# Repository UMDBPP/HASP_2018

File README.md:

# HASP_2018
2018 HASP payload with microphones and a dropped module.

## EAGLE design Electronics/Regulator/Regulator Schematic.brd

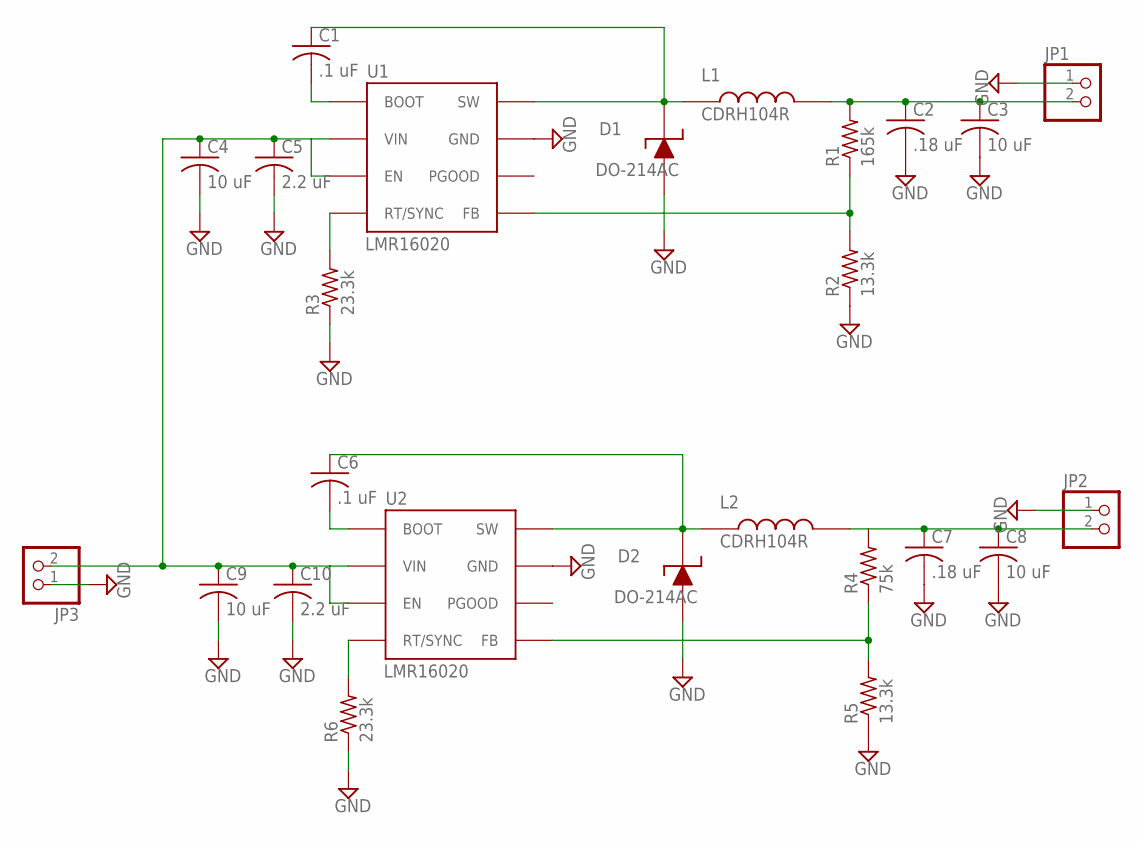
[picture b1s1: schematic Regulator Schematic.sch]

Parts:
C1, C6: .1 uF; C0603
C2, C7: .18 uF; C0603
C3, C8: 10 uF; C0603
C4, C9: 10 uF; C1210
C5, C10: 2.2 uF; C1210
D1, D2: DO-214AC
JP1, JP2, JP3: PINHD-1X2; 1X02
L1, L2: CDRH104R
R1: 165k; R0603
R2, R5: 13.3k; R0603
R3, R6: 23.3k; R0603
R4: 75k; R0603
U1, U2: LMR16020; SO8

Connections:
GND: C2.2, C3.2, C4.2, C5.2, C7.2, C8.2, C9.2, C10.2, D1.P$1, D2.P$1, JP1.1, JP2.1, JP3.1, R2.1, R3.1, R5.1, R6.1, U1.P$7 (GND), U1.PAD (GND), U2.P$7 (GND), U2.PAD (GND)
IN: C4.1, C5.1, C9.1, C10.1, JP3.2, U1.P$2 (VIN), U1.P$3 (EN), U2.P$2 (VIN), U2.P$3 (EN)
unnamed: R6.2, U2.P$4 (RT/SYNC)
unnamed: R3.2, U1.P$4 (RT/SYNC)
unnamed: C1.2, U1.P$1 (BOOT)
unnamed: C1.1, D1.P$2, L1.P$1, U1.P$8 (SW)
unnamed: R1.1, R2.2, U1.P$5 (FB)
unnamed: C6.2, U2.P$1 (BOOT)
unnamed: C6.1, D2.P$2, L2.P$1, U2.P$8 (SW)
unnamed: R4.1, R5.2, U2.P$5 (FB)
unnamed: C2.1, C3.1, JP1.2, L1.P$2, R1.2
unnamed: C7.1, C8.1, JP2.2, L2.P$2, R4.2

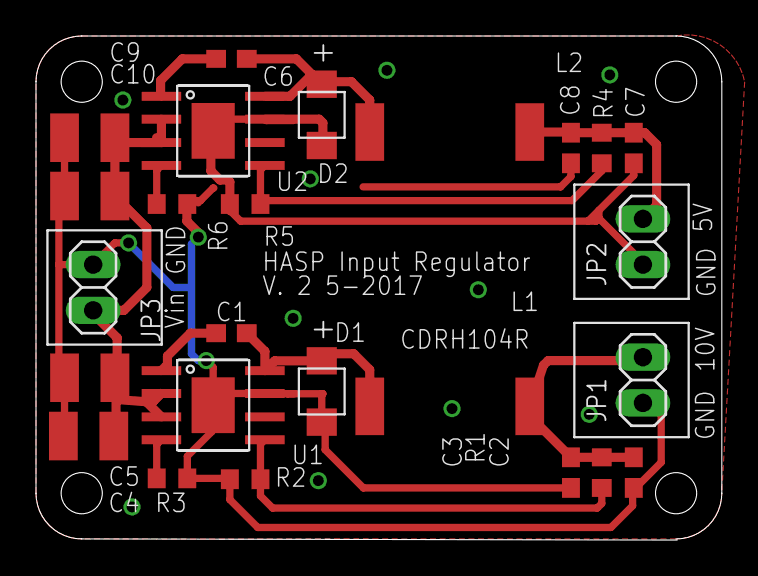
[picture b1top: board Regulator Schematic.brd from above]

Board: 2 copper layers, 38.1 x 28.0 mm, 25 parts (0 on the bottom side), 12 nets.

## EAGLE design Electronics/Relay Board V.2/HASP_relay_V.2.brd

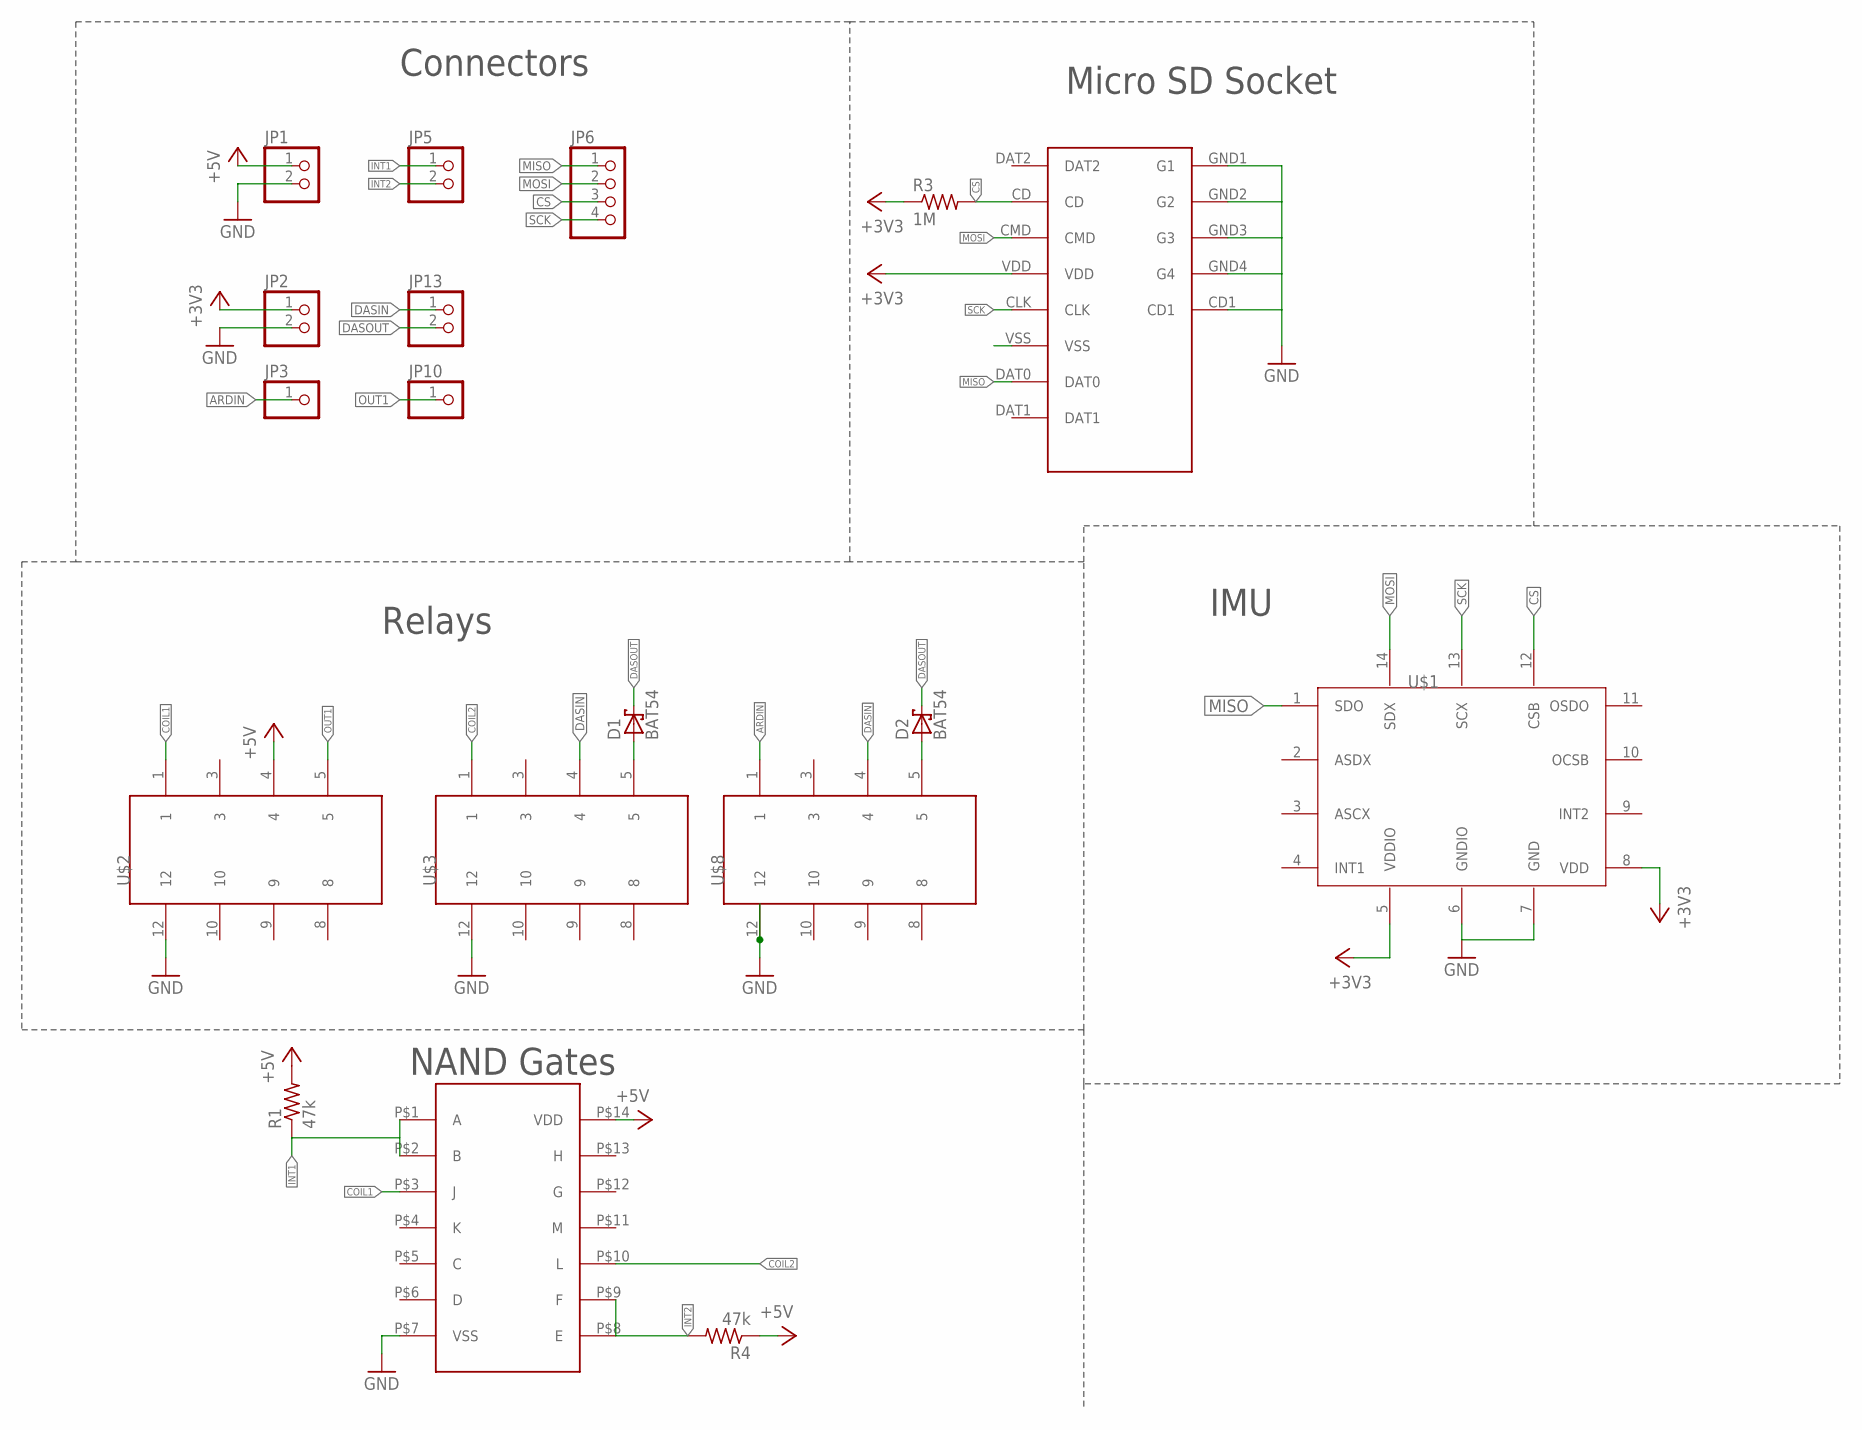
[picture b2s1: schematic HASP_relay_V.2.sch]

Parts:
D1, D2: BAT54; SOT23
JP1, JP2, JP5, JP13: PINHD-1X2; 1X02
JP3, JP10: PINHD-1X1; 1X01
JP6: PINHD-1X4; 1X04
R1, R4: 47k; RESC1608X50N
R3: 1M; R0603
U$1: BMI160; IMU
U$2, U$3, U$8: EC2; EC2-5SNU
U$4: MICRO_SD; MICRO_SD_HINGED
U$5: CD4093BE

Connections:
+3V3: JP2.1, R3.1, U$1.5 (VDDIO), U$1.8 (VDD), U$4.VDD
+5V: JP1.1, R1.2, R4.1, U$2.4, U$5.P$14 (VDD)
ARDIN: JP3.1, U$8.1
COIL1: U$2.1, U$5.P$3 (J)
COIL2: U$3.1, U$5.P$10 (L)
CS: JP6.3, R3.2, U$1.12 (CSB), U$4.CD
DASIN: JP13.1, U$3.4, U$8.4
DASOUT: D1.3 (K), D2.3 (K), JP13.2
GND: JP1.2, JP2.2, U$1.6 (GNDIO), U$1.7 (GND), U$2.12, U$3.12, U$4.CD1, U$4.GND1 (G1), U$4.GND2 (G2), U$4.GND3 (G3), U$4.GND4 (G4), U$5.P$7 (VSS), U$8.12
INT1: JP5.1, U$5.P$1 (A), U$5.P$2 (B)
INT2: JP5.2, R4.2, U$5.P$8 (E), U$5.P$9 (F)
MISO: JP6.1, U$1.1 (SDO), U$4.DAT0
MOSI: JP6.2, U$1.14 (SDX), U$4.CMD
unnamed: D1.1 (A), U$3.5
unnamed: D2.1 (A), U$8.5
OUT1: JP10.1, U$2.5
SCK: JP6.4, U$1.13 (SCX), U$4.CLK

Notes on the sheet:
NAND Gates
Relays
Connectors
IMU
Micro SD Socket

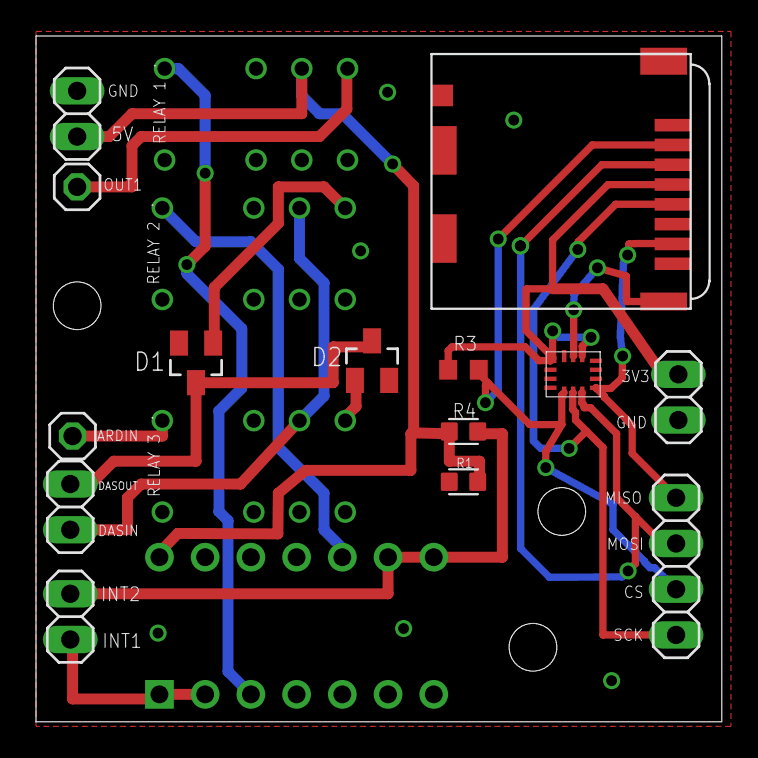
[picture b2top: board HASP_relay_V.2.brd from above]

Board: 2 copper layers, 38.1 x 38.1 mm, 18 parts (0 on the bottom side), 17 nets.

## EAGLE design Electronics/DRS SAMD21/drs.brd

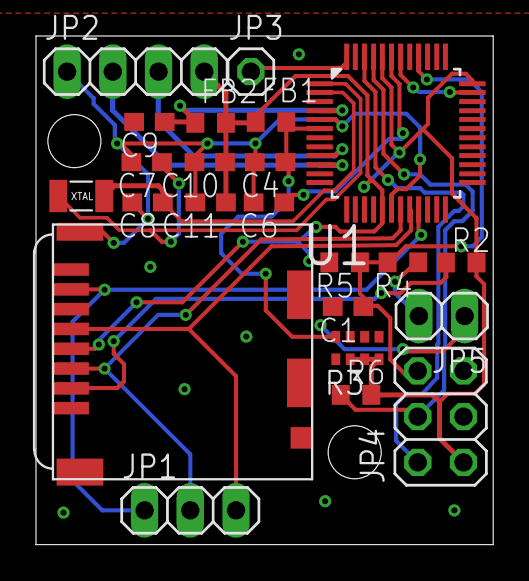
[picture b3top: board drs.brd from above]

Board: 2 copper layers, 25.4 x 28.3 mm, 23 parts (0 on the bottom side), 18 nets.

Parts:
C1, C9: 100nF; C0603
C4: 10uF; C0603
C6: 1uF; C0603
C7, C8, C10, C11: 6.8pF; C0603
FB1, FB2: 0603
JP1: 1X03
JP2: 1X04
JP3: 1X01
JP4: 2X03
JP5: 1X02
R2: 1M; R0603
R3: 100nF; 0603-ARV
R4: 330; R0603
R5, R6: 10k; R0603
U1: ATSAMD21G18; 48-TQFP
U$1: MICRO_SD; MICRO_SD_HINGED
XTAL1: 2-SMD

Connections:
+3V3: C10.1, C11.1, FB1.1, FB2.2, JP2.4, JP4.1, R2.2, R3.2, R3.3, R3.4, R5.2, R6.2, U1.17, U1.36, U1.44, U$1.VDD
AIN1: JP2.3, U1.9
AIN2: JP2.2, U1.10
GND: C1.2, C4.2, C6.2, C7.2, C8.2, C9.2, C10.2, C11.2, JP2.1, JP4.5, JP5.1, R3.1, R3.5, R3.6, R3.7, U1.5, U1.18, U1.35, U1.42, U$1.CD1, U$1.GND1, U$1.GND2, U$1.GND3, U$1.GND4, U$1.VSS
LED: JP3.1, U1.48
MISO: JP1.1, U1.21, U$1.DAT0
MOSI: JP1.2, U1.19, U$1.CMD
unnamed: R2.1, U$1.CD
unnamed: C6.1, U1.43
unnamed: C4.1, FB1.2, R3.8, U1.6
unnamed: JP5.2, R4.1
RESET: C1.1, JP4.6, R4.2, R5.1, U1.40
SCK: JP1.3, U1.20, U$1.CLK
SWDCLK: JP4.4, R6.1, U1.45
SWDIO: JP4.2, U1.46
VREFA: C9.1, FB2.1, U1.4
XIN32: C7.1, U1.1, XTAL1.P2
XOUT32: C8.1, U1.2, XTAL1.P1

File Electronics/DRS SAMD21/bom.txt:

Partlist exported from C:/UMD/BPP/HASP/2018/HASP_2018/Electronics/DRS SAMD21/drs.sch at 7/9/2018 5:26

Qty Value       Device                 Package         Parts            Description                
1               ABS07AIG-32.768KHZ-1-T 2-SMD           XTAL1                                       
1               C-USC0603              C0603           C1               CAPACITOR, American symbol 
2               FERRITE_BEAD-0603      0603            FB1, FB2                                    
1               PINHD-1X1              1X01            JP3              PIN HEADER                 
1               PINHD-1X2              1X02            JP5              PIN HEADER                 
1               PINHD-1X3              1X03            JP1              PIN HEADER                 
1               PINHD-1X4              1X04            JP2              PIN HEADER                 
1               PINHD-2X3              2X03            JP4              PIN HEADER                 
2               R-US_R0603             R0603           R4, R5           RESISTOR, American symbol  
1   100nF       C-USC0603              C0603           C9               CAPACITOR, American symbol 
1   100nF       RESISTOR-ARRAY0603-ARV 0603-ARV        R3               Array Chip Resistor        
1   10k         R-US_R0603             R0603           R6               RESISTOR, American symbol  
1   10uF        C-USC0603              C0603           C4               CAPACITOR, American symbol 
1   1M          R-US_R0603             R0603           R2               RESISTOR, American symbol  
1   1uF         C-USC0603              C0603           C6               CAPACITOR, American symbol 
4   6.8pF       C-USC0603              C0603           C7, C8, C10, C11 CAPACITOR, American symbol 
1   ATSAMD21G18 ATSAMD21G18            48-TQFP         U1                                          
1   MICRO_SD    MICRO_SD               MICRO_SD_HINGED U$1

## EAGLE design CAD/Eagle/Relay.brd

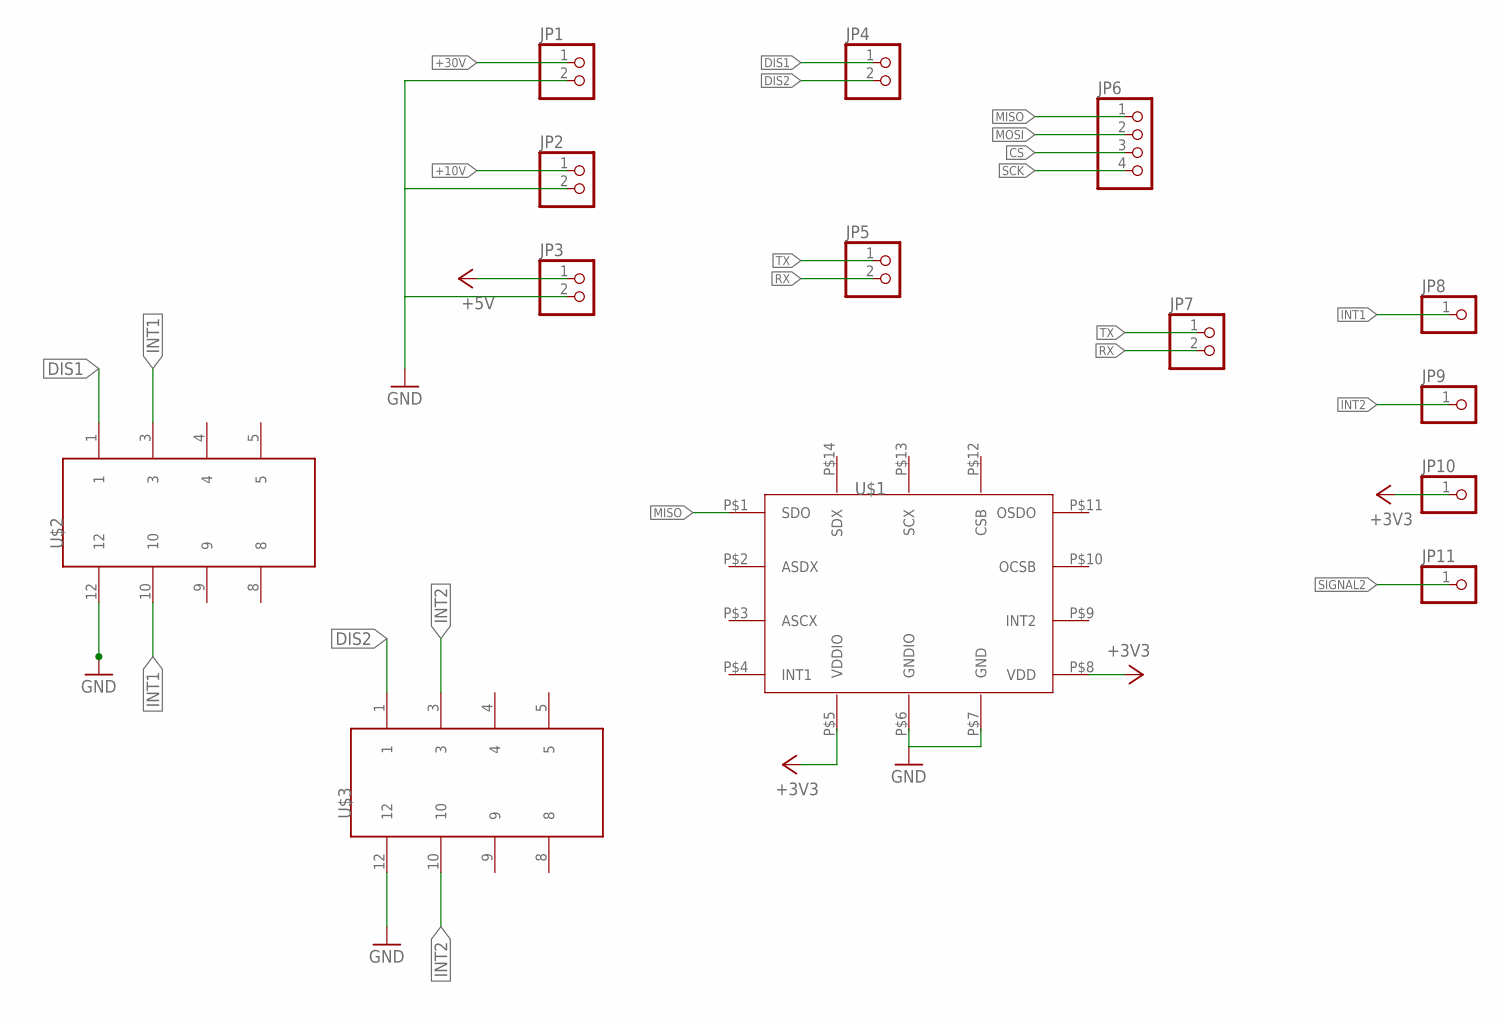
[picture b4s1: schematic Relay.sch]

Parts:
JP1, JP2, JP3, JP4, JP5, JP7: PINHD-1X2; 1X02
JP6: PINHD-1X4; 1X04
JP8, JP9, JP10, JP11: PINHD-1X1; 1X01
U$1: BMI160; IMU
U$2, U$3: EC2; EC2-5SNU

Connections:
+3V3: JP10.1, U$1.P$8 (VDD)
+5V: JP3.1
+10V: JP2.1
+30V: JP1.1
CS: JP6.3
DIS1: JP4.1, U$2.1
DIS2: JP4.2, U$3.1
GND: JP1.2, JP2.2, JP3.2, U$1.P$7 (GND), U$2.12, U$3.12
GNDIO: U$1.P$6 (GNDIO)
INT1: JP8.1, U$2.3, U$2.10
INT2: JP9.1, U$3.3, U$3.10
MISO: JP6.1, U$1.P$1 (SDO)
MOSI: JP6.2
RX: JP5.2, JP7.2
SCK: JP6.4
SIGNAL2: JP11.1
TX: JP5.1, JP7.1

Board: 2 copper layers, 14 parts (0 on the bottom side), 9 nets, no tracks yet.

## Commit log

2017-12-15 Initial CAD
2017-12-16 updated cad
2018-04-11 Initial Relay Board Schematic
2018-04-20 fixed rev 1 drs
2018-05-04 Relay Board
2018-05-07 gerbers
2018-05-30 new stuff
2018-06-11 Add files via upload
    Screw holes are a little offset, and need to add modifications to attach the drop mod to the actuator plate
2018-06-12 Add files via upload
    Adjustments made to drop box.
    Drill holes added to the upper plate.
    U-bolts and corresponding nuts added to drawing.
    Note: Heavy Gauge wire may suffice in place of a U-bolt and nut
2018-07-05 SAMD21 DRS
2018-07-08 Create New Relay Board
2018-07-08 last year's flight code
2018-07-09 I routed a board, and it's really tiny
2018-07-10 got rid of unnecessary things on relay board, fixed the SD card routing, set up rough pass of board size
2018-07-11 rerouted relay board, also put the power regulator in this repo from last years
2018-07-14 added drs fsw
2018-07-20 change write to write string instead of bytes. Also added flush
2018-07-22 uno code
2018-07-22 added das status message
2018-07-22 hcanges to serial code
2018-07-23 minor changes
2018-07-26 Add files via upload
    The version of Uno software from integration. Changes include refactored command handling and a new format for the downlink.
2018-07-26 Add files via upload
    Integration version of the nano software. Accounts for changes made to our discrete signaling and detection timing.
2018-07-28 software to check the HASP website and pull down new telemetry packets
2018-07-28 Added query to get payload number
2018-08-10 Working DRS code on an Arduino Nano
2018-08-11 added RNG voltage output for DRS interface
2018-08-12 HAAT arduino code with working DRS implementation
2018-08-15 changed flight serial baud back to 1200
2018-08-31 rewrote telem_parser script in python to make it better
2018-08-31 Updated to handle grabbing last few lines in previous file when a new file is created
2018-08-31 Added filewriting functionality
2018-08-31 fixed bug for first grab of telemetry

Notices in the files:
parts and their libraries:
SparkFun-Passives: Licensing: CC v3.0 Share-Alike You are welcome to use this library for commercial purposes.
